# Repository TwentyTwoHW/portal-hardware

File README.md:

# portal-hardware

Kicad project containing the Portal board design.

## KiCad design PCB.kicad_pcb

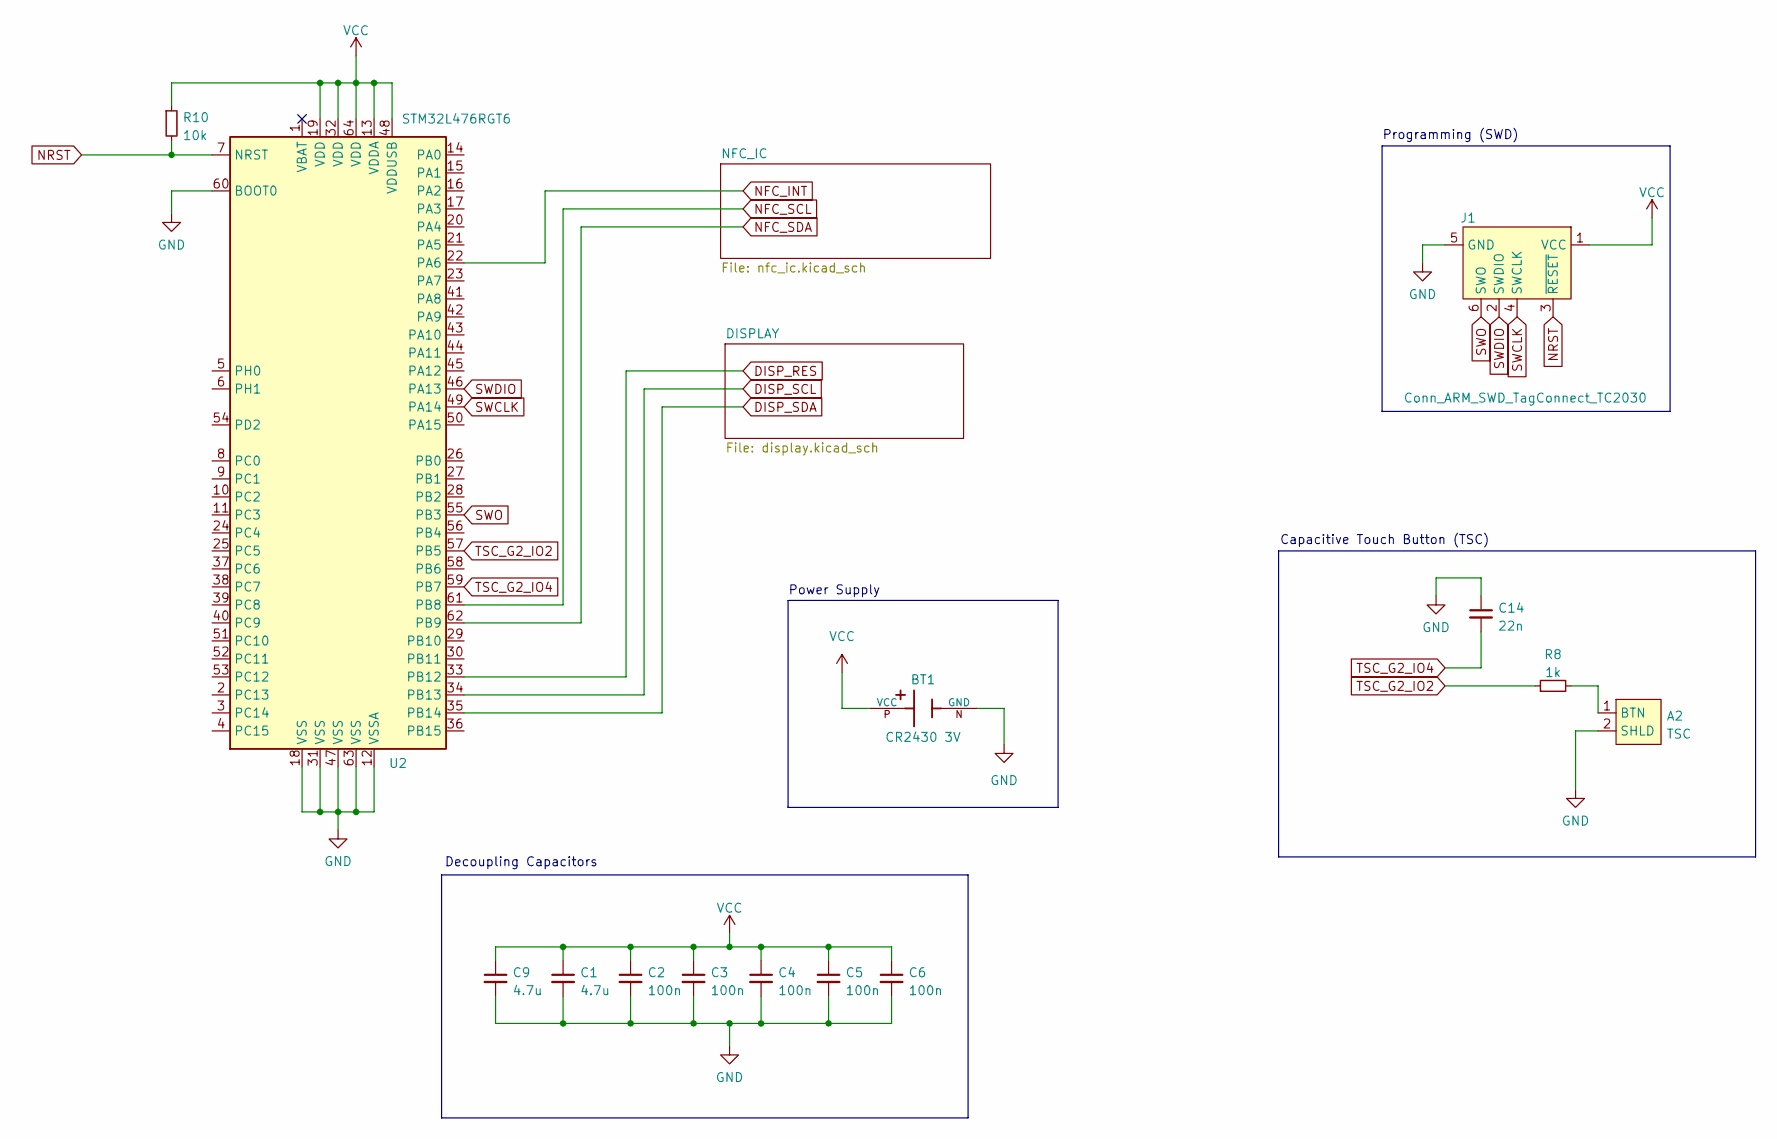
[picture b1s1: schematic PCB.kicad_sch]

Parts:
A2: TSC; TSC-Rectangle-25x16mm
BT1: CR2430 3V; BatteryHolder_Keystone_105_1x2430; PARTREV H
C1, C9: 4.7u; C_0805_2012Metric
C2, C3, C4, C5, C6: 100n; C_0603_1608Metric
C14: 22n; C_0603_1608Metric
J1: Conn_ARM_SWD_TagConnect_TC2030; Tag-Connect_TC2030-IDC-NL_2x03_P1.27mm_Vertical
R8: 1k; R_0603_1608Metric
R10: 10k; R_0603_1608Metric
U2: STM32L476RGT6; LQFP-64_10x10mm_P0.5mm

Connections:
DISP_RES: U2.33 (PB12); also elsewhere on the board
DISP_SCL: U2.34 (PB13); also elsewhere on the board
DISP_SDA: U2.35 (PB14); also elsewhere on the board
GND: A2.2 (SHLD), BT1.N (GND), C1.2, C2.2, C3.2, C4.2, C5.2, C6.2, C9.2, C14.1, J1.5 (GND), U2.12 (VSSA), U2.18 (VSS), U2.31 (VSS), U2.47 (VSS), U2.60 (BOOT0), U2.63 (VSS); also elsewhere on the board
NFC_INT: U2.22 (PA6); also elsewhere on the board
NFC_SCL: U2.61 (PB8); also elsewhere on the board
NFC_SDA: U2.62 (PB9); also elsewhere on the board
NRST: J1.3 (~RESET), R10.2, U2.7 (NRST)
unnamed: A2.1 (BTN), R8.2
SWCLK: J1.4 (SWCLK), U2.49 (PA14)
SWDIO: J1.2 (SWDIO), U2.46 (PA13)
SWO: J1.6 (SWO), U2.55 (PB3)
TSC_G2_IO2: R8.1, U2.57 (PB5)
TSC_G2_IO4: C14.2, U2.59 (PB7)
VCC: BT1.P (VCC), C1.1, C2.1, C3.1, C4.1, C5.1, C6.1, C9.1, J1.1 (VCC), R10.1, U2.13 (VDDA), U2.19 (VDD), U2.32 (VDD), U2.48 (VDDUSB), U2.64 (VDD); also elsewhere on the board

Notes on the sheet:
Programming (SWD)
Power Supply
Capacitive Touch Button (TSC)
Decoupling Capacitors

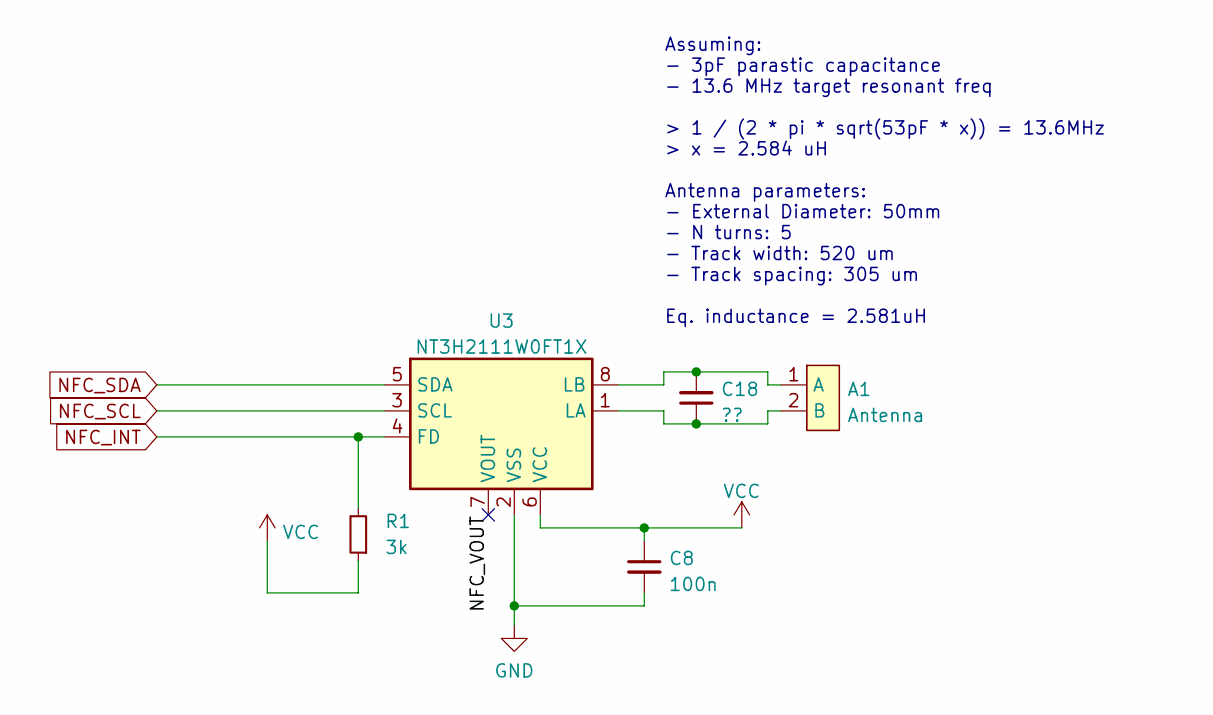
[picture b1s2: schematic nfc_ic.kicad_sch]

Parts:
A1: Antenna; Antenna-Round-13.8MHz-53pF-Class3-50mm
C8: 100n; C_0603_1608Metric
C18: ??; C_0603_1608Metric
R1: 3k; R_0603_1608Metric
U3: NT3H2111W0FT1X; SOT96-1

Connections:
/NFC_IC/NFC_VOUT: U3.7 (VOUT)
GND: C8.2, U3.2 (VSS); also elsewhere on the board
NFC_INT: R1.2, U3.4 (FD); also elsewhere on the board
NFC_SCL: U3.3 (SCL); also elsewhere on the board
NFC_SDA: U3.5 (SDA); also elsewhere on the board
unnamed: A1.1 (A), C18.2, U3.8 (LB)
unnamed: A1.2 (B), C18.1, U3.1 (LA)
VCC: C8.1, R1.1, U3.6 (VCC); also elsewhere on the board

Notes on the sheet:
Assuming: - 3pF parastic capacitance - 13.6 MHz target resonant freq > 1 / (2 * pi * sqrt(53pF * x)) = 13.6MHz > x = 2.584 uH Antenna parameters: - External Diameter: 50mm - N turns: 5 - Track width: 520 um - Track spacing: 305 um Eq. inductance = 2.581uH

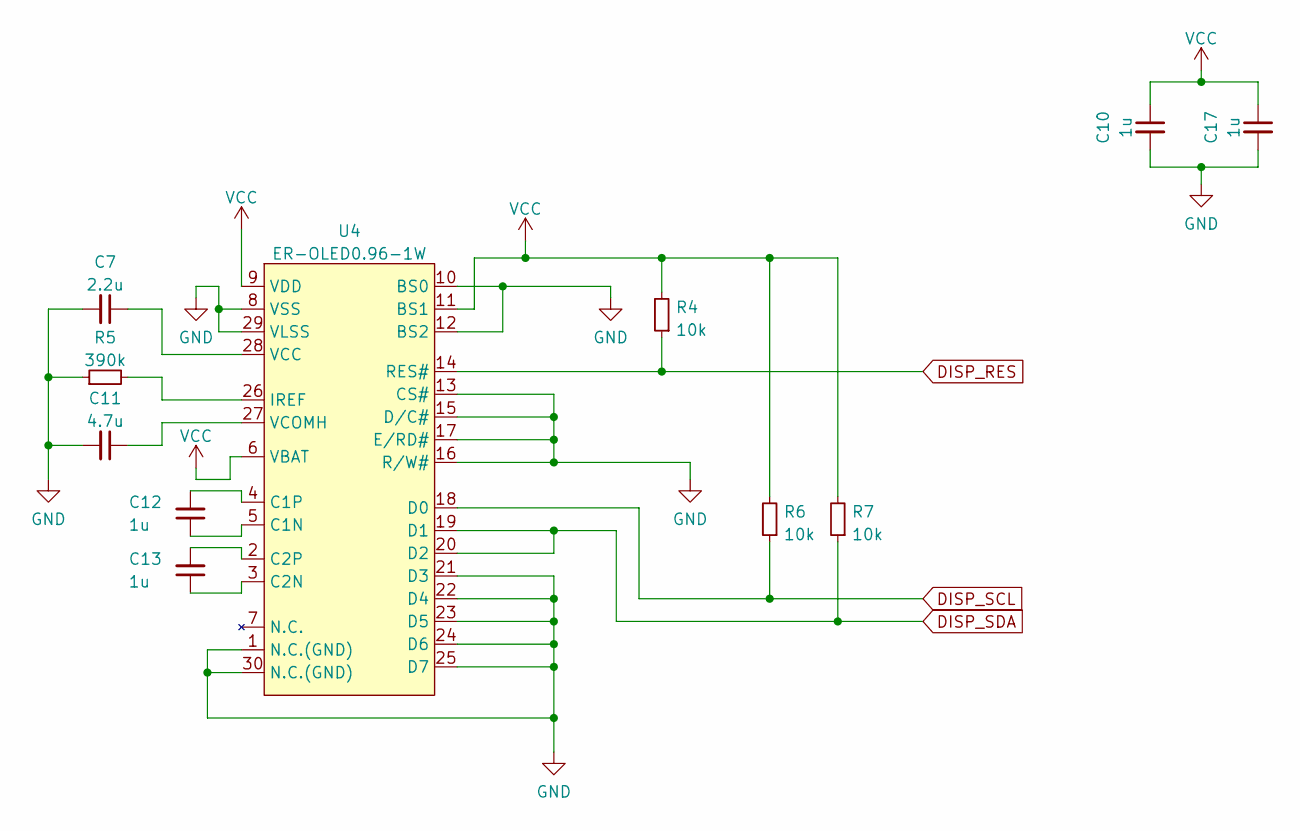
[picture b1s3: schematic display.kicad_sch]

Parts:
C7: 2.2u; C_0603_1608Metric
C10, C12, C13, C17: 1u; C_0603_1608Metric
C11: 4.7u; C_0805_2012Metric
R4, R6, R7: 10k; R_0603_1608Metric
R5: 390k; R_0603_1608Metric
U4: ER-OLED0.96-1W; OLED-128O064D-WITH-FP

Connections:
DISP_RES: R4.1, U4.14 (RES#); also elsewhere on the board
DISP_SCL: R6.1, U4.18 (D0); also elsewhere on the board
DISP_SDA: R7.1, U4.19 (D1), U4.20 (D2); also elsewhere on the board
GND: C7.2, C10.2, C11.2, C17.2, R5.1, U4.1 (N.C.(GND)), U4.8 (VSS), U4.10 (BS0), U4.12 (BS2), U4.13 (CS#), U4.15 (D/C#), U4.16 (R/W#), U4.17 (E/RD#), U4.21 (D3), U4.22 (D4), U4.23 (D5), U4.24 (D6), U4.25 (D7), U4.29 (VLSS), U4.30 (N.C.(GND)); also elsewhere on the board
unnamed: C12.1, U4.5 (C1N)
unnamed: C12.2, U4.4 (C1P)
unnamed: C13.1, U4.3 (C2N)
unnamed: C13.2, U4.2 (C2P)
unnamed: R5.2, U4.26 (IREF)
unnamed: C7.1, U4.28 (VCC)
unnamed: C11.1, U4.27 (VCOMH)
VCC: C10.1, C17.1, R4.2, R6.2, R7.2, U4.6 (VBAT), U4.9 (VDD), U4.11 (BS1); also elsewhere on the board

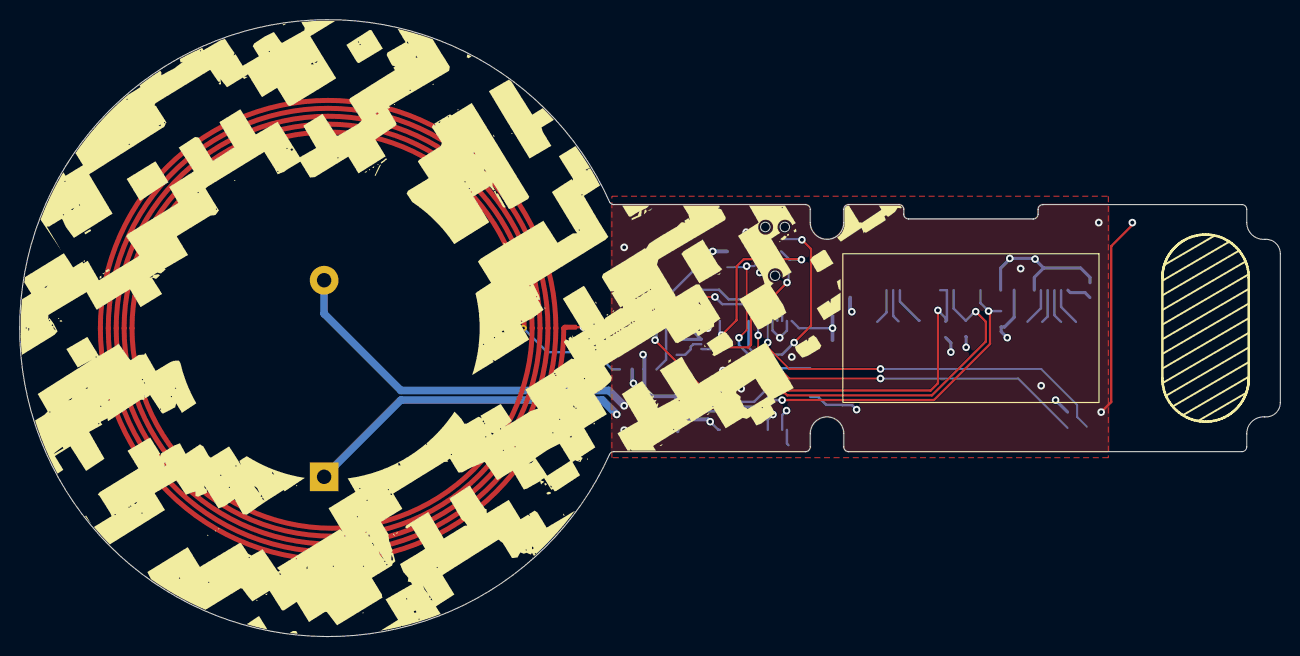
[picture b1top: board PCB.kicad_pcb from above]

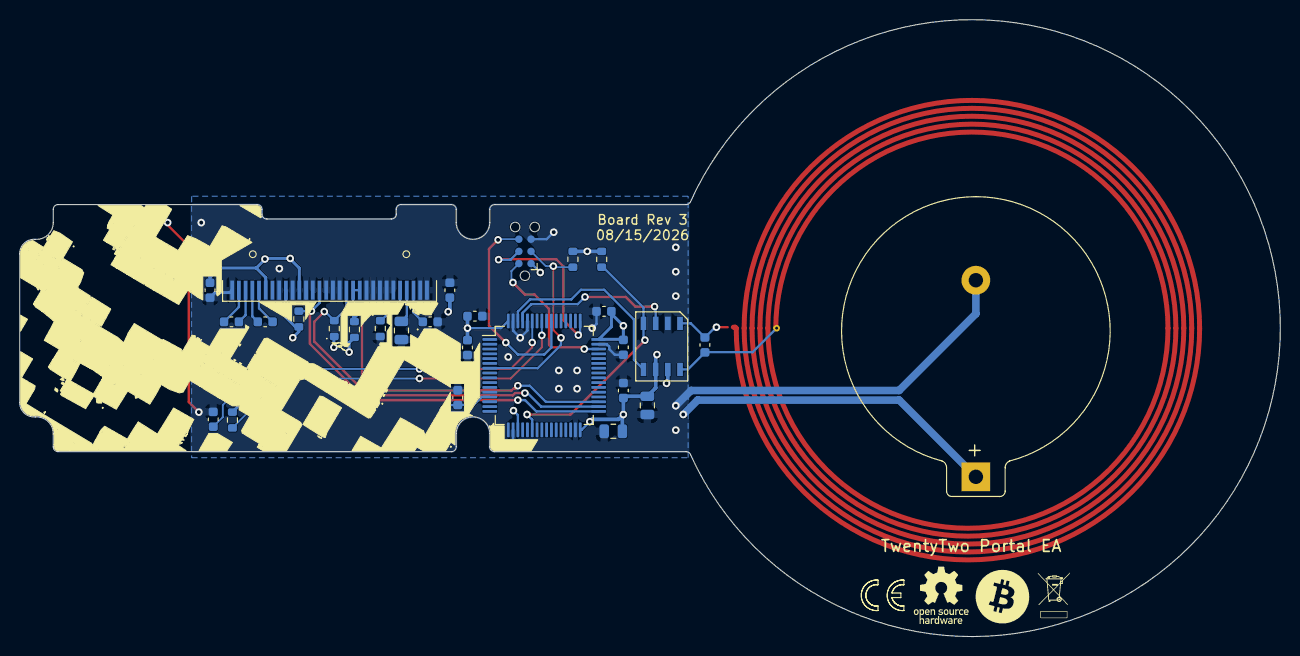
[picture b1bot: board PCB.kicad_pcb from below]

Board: 4 copper layers, 131.4 x 64.3 mm, 30 parts (29 on the bottom side), 24 nets.

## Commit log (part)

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2024-07-16 Add board REV-D
    Revision D changes the mounting holes so that we can fit screws to
    assemble the two case pieces.
    Also add required compliance logos on the back.
2024-07-16 Add STEP files of the case
2024-07-16 Update SVG plot
2024-07-16 Add SVG background when in light color mode
